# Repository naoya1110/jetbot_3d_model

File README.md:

# JetBot 3D Model

## 部品リスト
| 部品 | Link | 備考 |
| ---- | ---- | ---- |
| Jetson Nano 開発者キット B01 | [Switch Science](https://www.switch-science.com/products/6239)|  |
| FeatherWing - DC/ステッピングモータードライバ | [Switch Science](https://www.switch-science.com/products/6457) |  |
| Adafruit PiOLED | [Switch Science](https://www.switch-science.com/products/3393) |  |
| IMX219カメラ | [Amazon](https://www.amazon.co.jp/dp/B08K2SRZNX/) |  |
| WiFiドングル | [Amazon](https://www.amazon.co.jp/dp/B07MXHJ6KB/) |  |
| DCモーター + 車輪 | [Amazon](https://www.amazon.co.jp/dp/B09F92W3V3/) |  |
| モバイルバッテリー | [INIU](https://www.iniupower.com/iniu-portable-charger-10000mah-power-bank-led-display-dual-usb-output/) | Size 130 x 68 x 15 mm |

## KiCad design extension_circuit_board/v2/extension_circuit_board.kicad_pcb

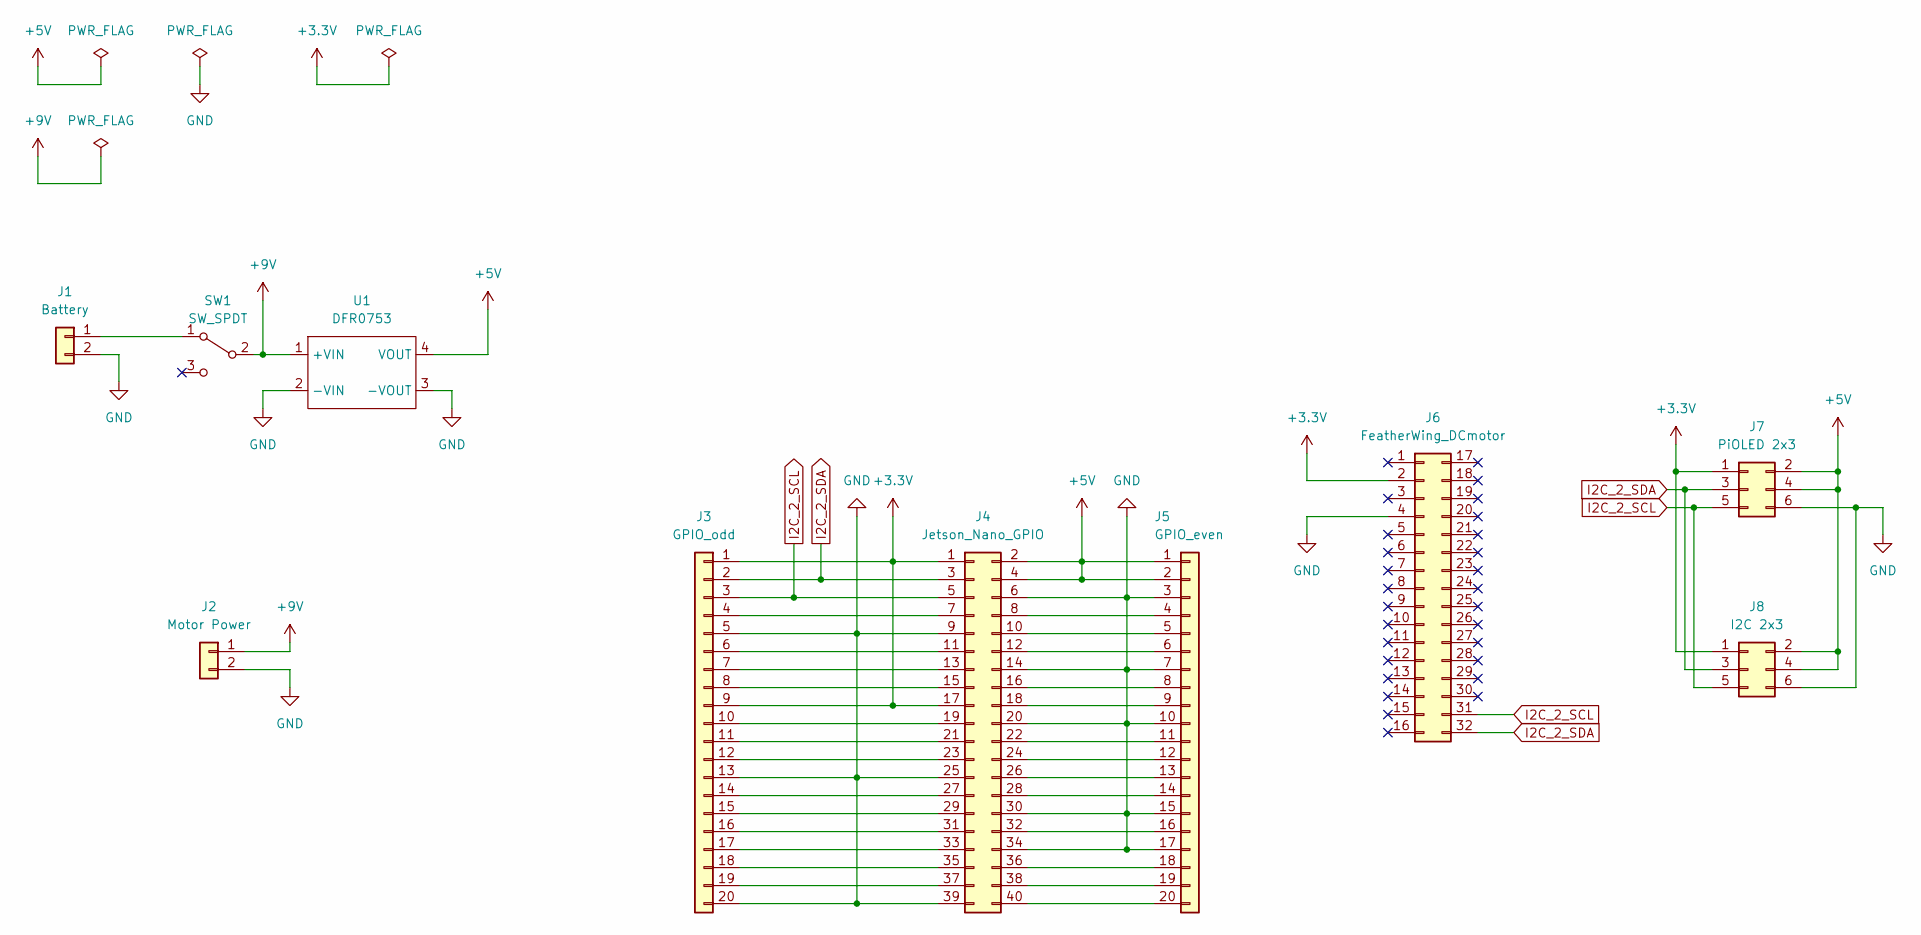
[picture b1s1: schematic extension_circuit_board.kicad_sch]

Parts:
J1: Battery; Jetson Nano Power
J2: Motor Power; Jetson Nano Power
J3: GPIO_odd; PinHeader_1x20_P2.54mm_Vertical
J4: Jetson_Nano_GPIO; PinHeader_2x20_P2.54mm_Vertical
J5: GPIO_even; PinHeader_1x20_P2.54mm_Vertical
J6: FeatherWing_DCmotor; FeatherWing_DC_Motor_Driver
J7: PiOLED 2x3; PinHeader_2x03_P2.54mm_Vertical
J8: I2C 2x3; PinHeader_2x03_P2.54mm_Vertical
SW1: SW_SPDT; AE_SW_TOGGLE
U1: DFR0753

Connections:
+3.3V: J3.1, J3.9, J4.1, J4.17, J6.2, J7.1, J8.1; also elsewhere on the board
+5V: J4.2, J4.4, J5.1, J5.2, J7.2, J7.4, J8.2, J8.4, U1.4 (VOUT); also elsewhere on the board
+9V: J2.1, SW1.2 (B), U1.1 (+VIN)
GND: J1.2, J2.2, J3.5, J3.13, J3.20, J4.6, J4.9, J4.14, J4.20, J4.25, J4.30, J4.34, J4.39, J5.3, J5.7, J5.10, J5.15, J5.17, J6.4, J7.6, J8.6, U1.2 (-VIN), U1.3 (-VOUT); also elsewhere on the board
I2C_2_SCL: J3.3, J4.5, J6.31, J7.5, J8.5; also elsewhere on the board
I2C_2_SDA: J3.2, J4.3, J6.32, J7.3, J8.3; also elsewhere on the board
unnamed: J3.4, J4.7
unnamed: J3.6, J4.11
unnamed: J3.7, J4.13
unnamed: J3.8, J4.15
unnamed: J3.10, J4.19
unnamed: J3.11, J4.21
unnamed: J3.12, J4.23
unnamed: J3.14, J4.27
unnamed: J3.15, J4.29
unnamed: J3.16, J4.31
unnamed: J3.17, J4.33
unnamed: J3.18, J4.35
unnamed: J3.19, J4.37
unnamed: J4.8, J5.4
unnamed: J4.10, J5.5
unnamed: J4.12, J5.6
unnamed: J4.16, J5.8
unnamed: J4.18, J5.9
unnamed: J4.22, J5.11
unnamed: J4.24, J5.12
unnamed: J4.26, J5.13
unnamed: J4.28, J5.14
unnamed: J4.32, J5.16
unnamed: J4.36, J5.18
unnamed: J4.38, J5.19
unnamed: J4.40, J5.20
unnamed: J1.1, SW1.1 (A)

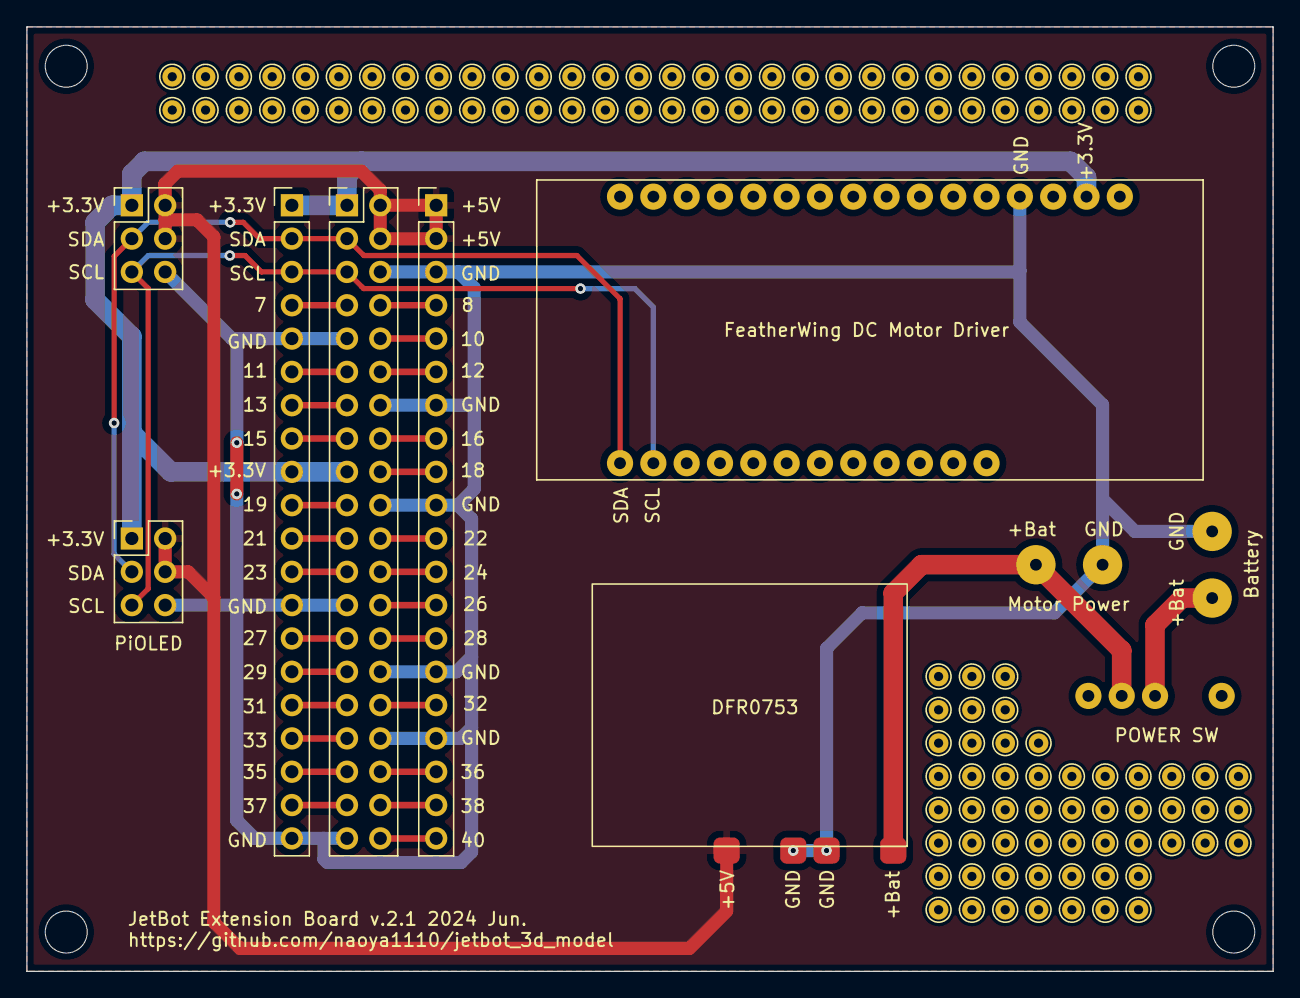
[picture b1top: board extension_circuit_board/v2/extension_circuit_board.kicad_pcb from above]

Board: 2 copper layers, 95.0 x 72.0 mm, 10 parts (0 on the bottom side), 33 nets.

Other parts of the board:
PiOLED: I2C 2x3; PinHeader_2x03_P2.54mm_Vertical

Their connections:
+3.3V: PiOLED.1; also elsewhere on the board
+5V: PiOLED.2, PiOLED.4; also elsewhere on the board
GND: PiOLED.6; also elsewhere on the board
I2C_2_SCL: PiOLED.5; also elsewhere on the board
I2C_2_SDA: PiOLED.3; also elsewhere on the board

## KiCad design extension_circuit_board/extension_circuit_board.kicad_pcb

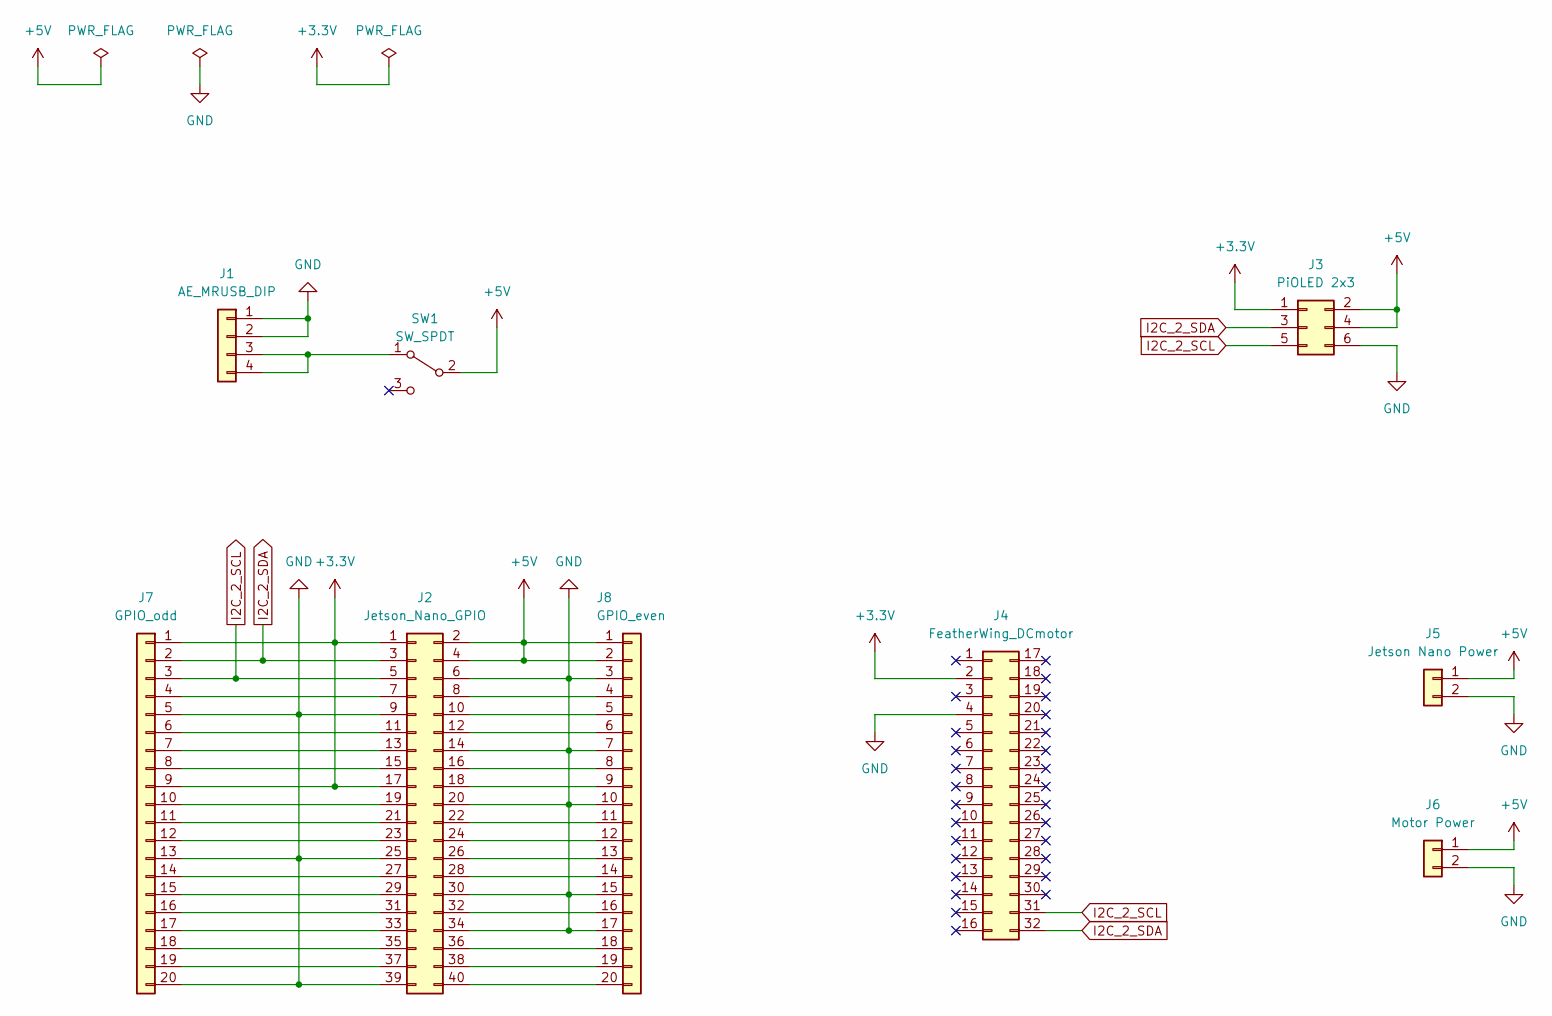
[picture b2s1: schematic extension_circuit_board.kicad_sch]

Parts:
J1: AE_MRUSB_DIP
J2: Jetson_Nano_GPIO; PinHeader_2x20_P2.54mm_Vertical
J3: PiOLED 2x3; PinHeader_2x03_P2.54mm_Vertical
J4: FeatherWing_DCmotor; FeatherWing_DC_Motor_Driver
J5: Jetson Nano Power
J6: Motor Power; Jetson Nano Power
J7: GPIO_odd; PinHeader_1x20_P2.54mm_Vertical
J8: GPIO_even; PinHeader_1x20_P2.54mm_Vertical
SW1: SW_SPDT; AE_SW_TOGGLE

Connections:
+3.3V: J2.1, J2.17, J3.1, J4.2, J7.1, J7.9
+5V: J2.2, J2.4, J3.2, J3.4, J5.1, J6.1, J8.1, J8.2, SW1.2 (B)
GND: J1.1, J1.2, J2.6, J2.9, J2.14, J2.20, J2.25, J2.30, J2.34, J2.39, J3.6, J4.4, J5.2, J6.2, J7.5, J7.13, J7.20, J8.3, J8.7, J8.10, J8.15, J8.17
I2C_2_SCL: J2.5, J3.5, J4.31, J7.3
I2C_2_SDA: J2.3, J3.3, J4.32, J7.2
unnamed: J1.3, J1.4, SW1.1 (A)
unnamed: J2.7, J7.4
unnamed: J2.8, J8.4
unnamed: J2.10, J8.5
unnamed: J2.11, J7.6
unnamed: J2.12, J8.6
unnamed: J2.13, J7.7
unnamed: J2.15, J7.8
unnamed: J2.16, J8.8
unnamed: J2.18, J8.9
unnamed: J2.19, J7.10
unnamed: J2.21, J7.11
unnamed: J2.22, J8.11
unnamed: J2.23, J7.12
unnamed: J2.24, J8.12
unnamed: J2.26, J8.13
unnamed: J2.27, J7.14
unnamed: J2.28, J8.14
unnamed: J2.29, J7.15
unnamed: J2.31, J7.16
unnamed: J2.32, J8.16
unnamed: J2.33, J7.17
unnamed: J2.35, J7.18
unnamed: J2.36, J8.18
unnamed: J2.37, J7.19
unnamed: J2.38, J8.19
unnamed: J2.40, J8.20

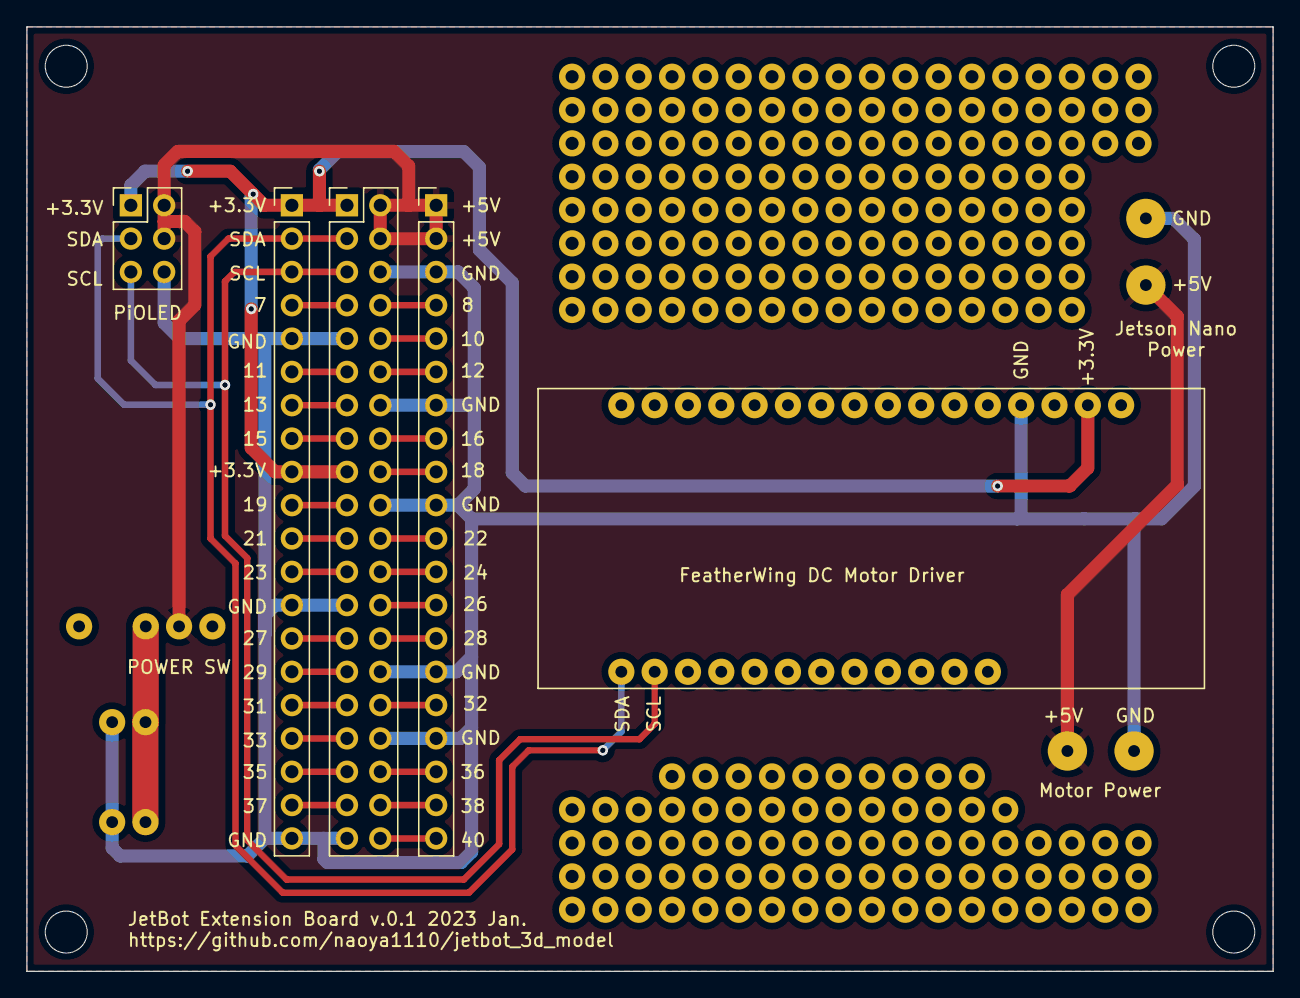
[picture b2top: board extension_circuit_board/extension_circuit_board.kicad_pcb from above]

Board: 2 copper layers, 95.0 x 72.0 mm, 9 parts (1 on the bottom side), 32 nets.

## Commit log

2022-11-15 uploaded
2023-12-05 add antenna fin model
